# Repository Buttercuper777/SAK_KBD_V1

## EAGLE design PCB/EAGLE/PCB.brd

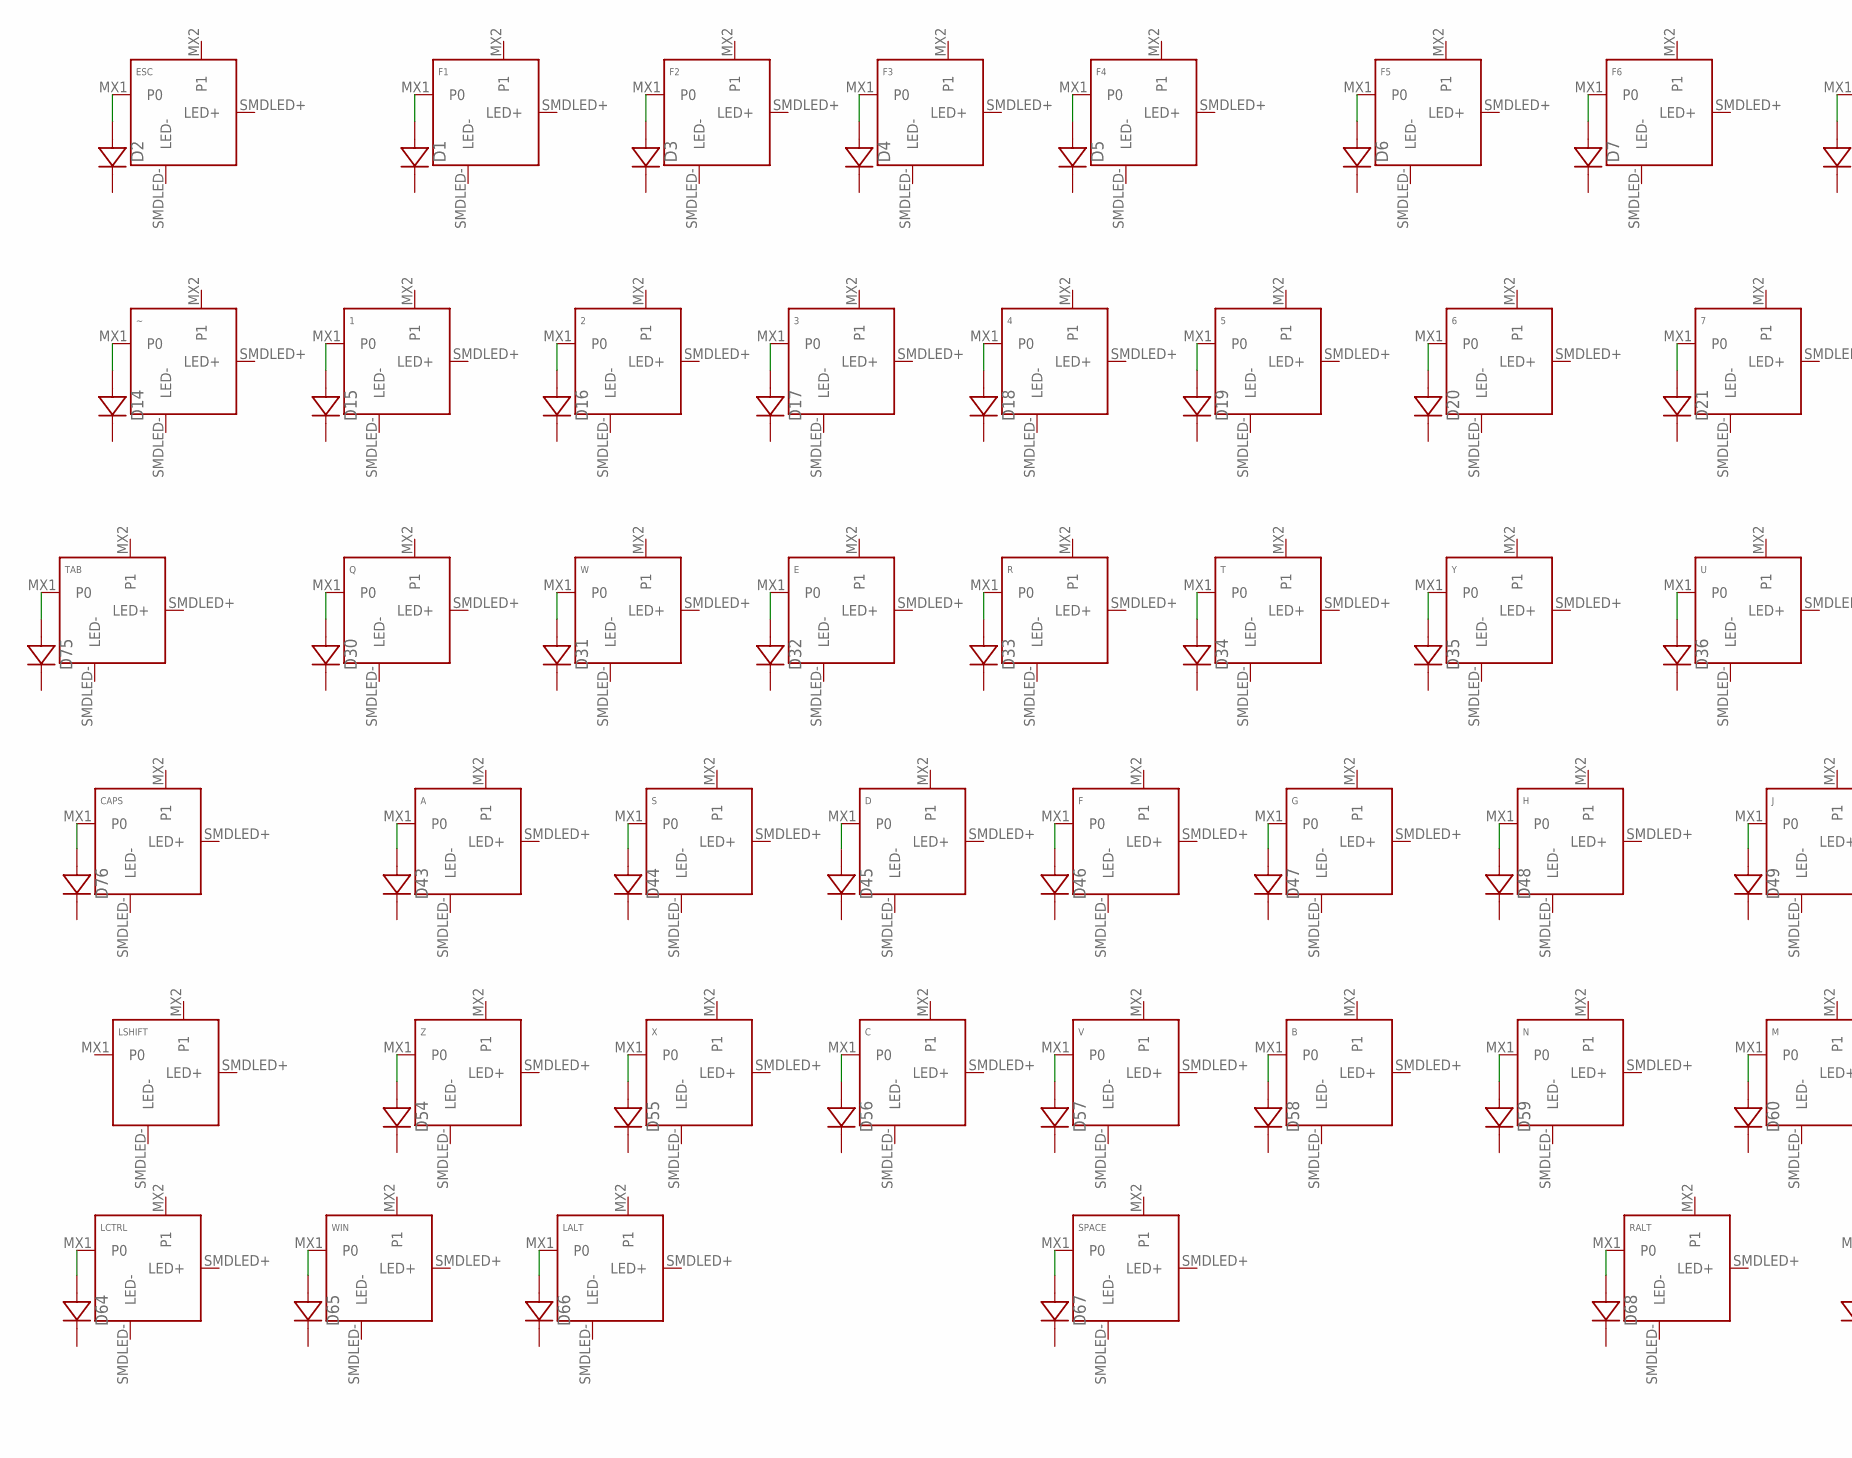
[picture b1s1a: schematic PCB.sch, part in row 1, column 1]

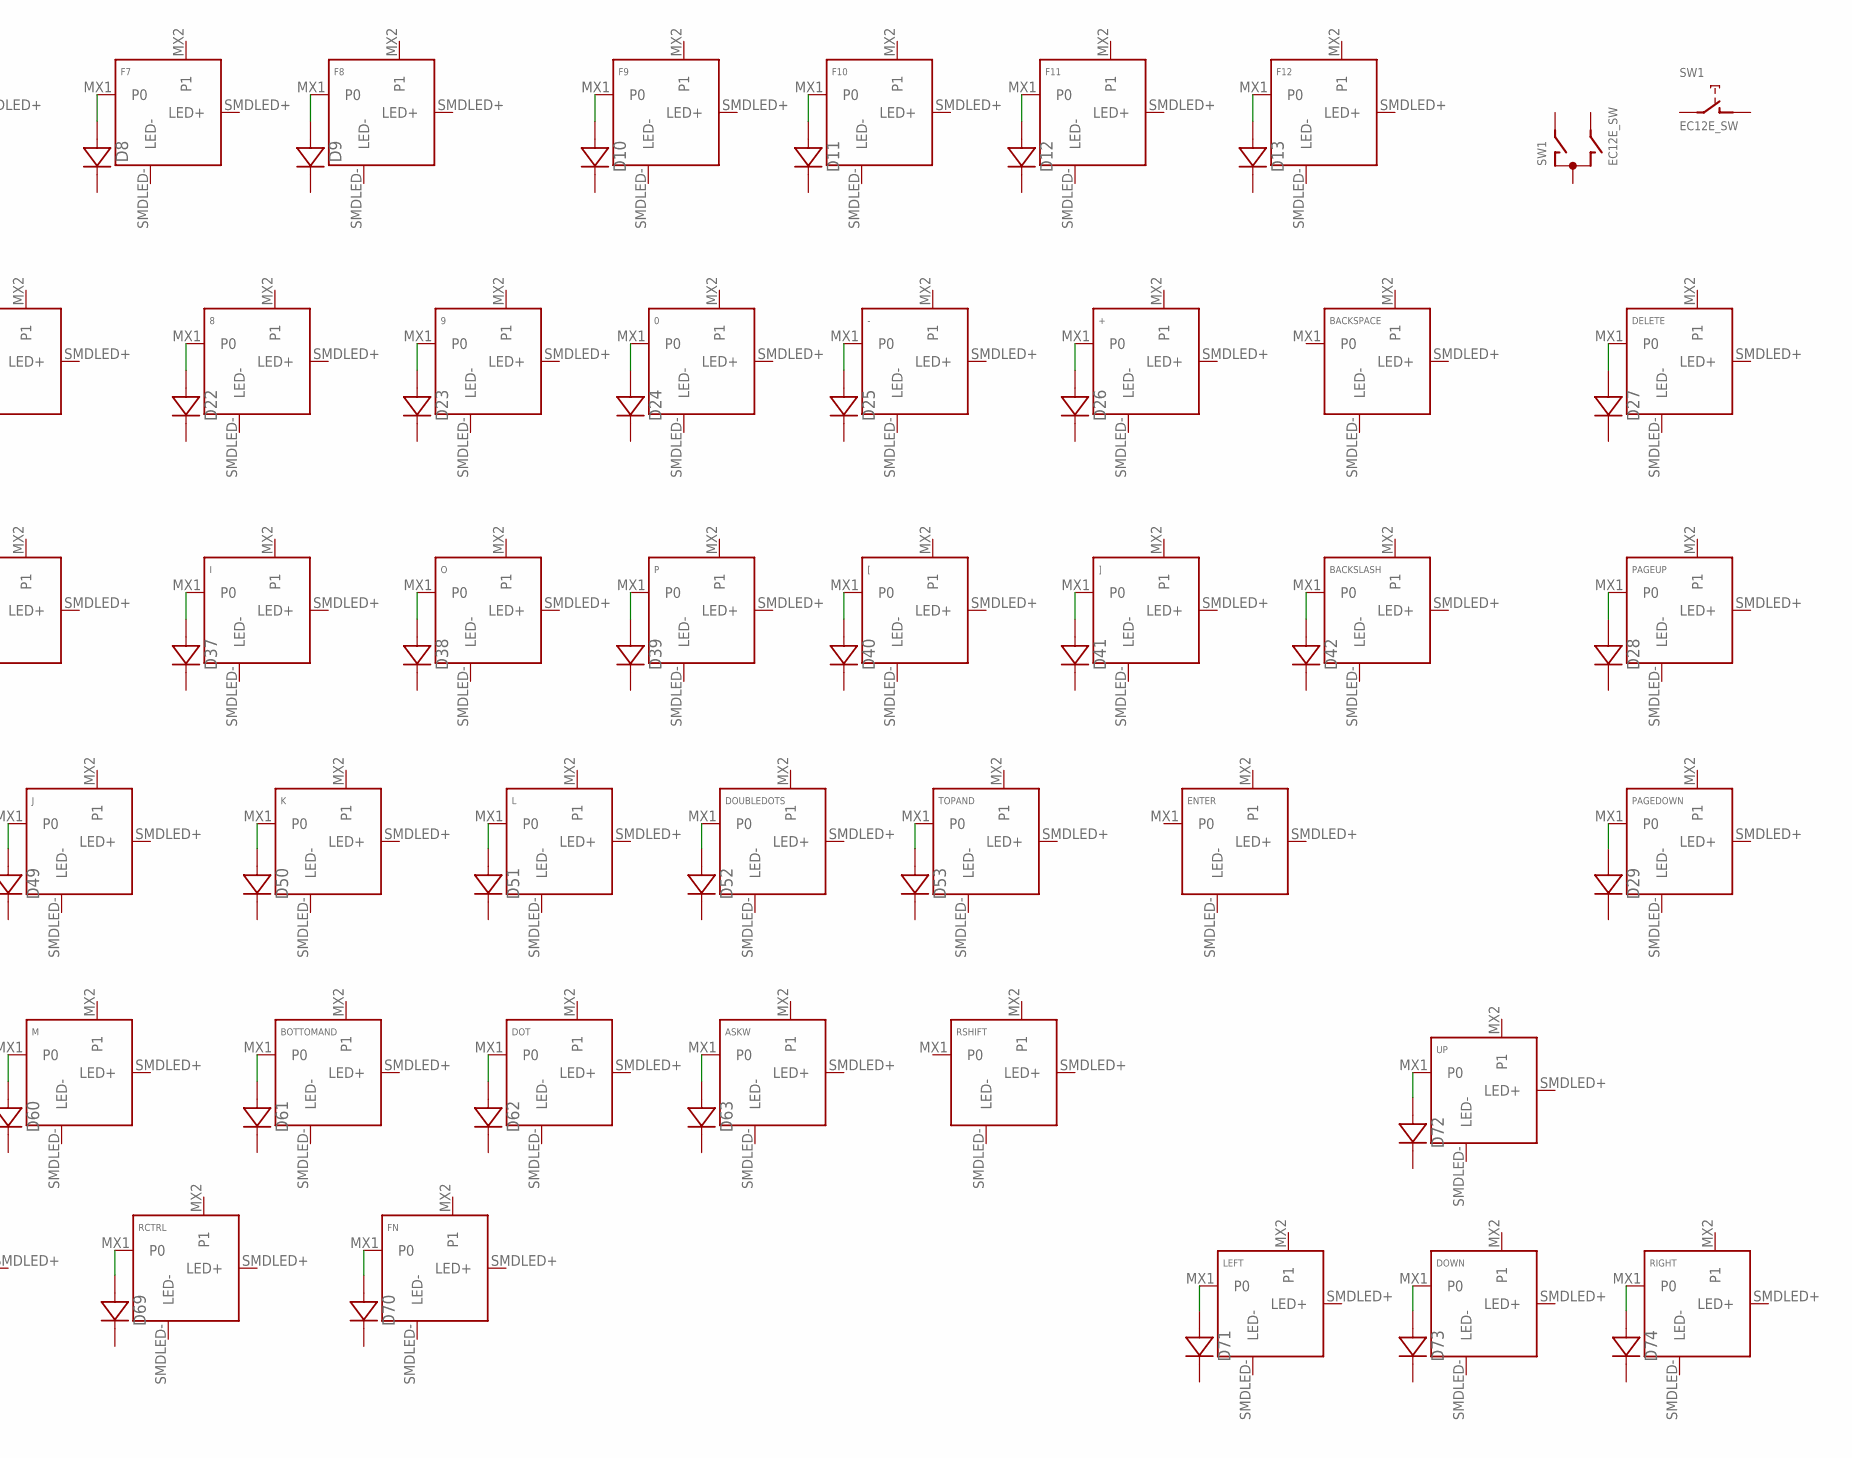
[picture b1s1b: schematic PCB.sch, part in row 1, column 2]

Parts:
0, 1, 2, 3, 4, 5, 6, 7, 8, 9: KEYSWITCH-SMDLED-MXHSPCB-1U-SMDLED; MXHSPCB-1U-SMDLED
+: KEYSWITCH-SMDLED-MXHSPCB-1U-SMDLED; MXHSPCB-1U-SMDLED
-: KEYSWITCH-SMDLED-MXHSPCB-1U-SMDLED; MXHSPCB-1U-SMDLED
A: KEYSWITCH-SMDLED-MXHSPCB-1U-SMDLED; MXHSPCB-1U-SMDLED
ASKW: KEYSWITCH-SMDLED-MXHSPCB-1U-SMDLED; MXHSPCB-1U-SMDLED
B: KEYSWITCH-SMDLED-MXHSPCB-1U-SMDLED; MXHSPCB-1U-SMDLED
BACKSLASH: KEYSWITCH-SMDLED-MXHSPCB-1U-SMDLED; MXHSPCB-1U-SMDLED
BACKSPACE: KEYSWITCH-SMDLED-MXHSPCB-2U-SMDLED; MXHSPCB-2U-SMDLED
BOTTOMAND: KEYSWITCH-SMDLED-MXHSPCB-1U-SMDLED; MXHSPCB-1U-SMDLED
C: KEYSWITCH-SMDLED-MXHSPCB-1U-SMDLED; MXHSPCB-1U-SMDLED
CAPS: KEYSWITCH-SMDLED-MXHSPCB-1U-SMDLED; MXHSPCB-1U-SMDLED
D: KEYSWITCH-SMDLED-MXHSPCB-1U-SMDLED; MXHSPCB-1U-SMDLED
D1, D2, D3, D4, D5, D6, D7, D8, D9, D10, D11, D12, D13, D14, D15, D16, D17, D18, D19, D20, D21, D22, D23, D24, D25, D26, D27, D28, D29, D30, D31, D32, D33, D34, D35, D36, D37, D38, D39, D40, D41, D42, D43, D44, D45, D46, D47, D48, D49, D50, D51, D52, D53, D54, D55, D56, D57, D58, D59, D60, D61, D62, D63, D64, D65, D66, D67, D68, D69, D70, D71, D72, D73, D74, D75, D76: DIODE-SOD-123; SOD-123
DELETE: KEYSWITCH-SMDLED-MXHSPCB-1U-SMDLED; MXHSPCB-1U-SMDLED
DOT: KEYSWITCH-SMDLED-MXHSPCB-1U-SMDLED; MXHSPCB-1U-SMDLED
DOUBLEDOTS: KEYSWITCH-SMDLED-MXHSPCB-1U-SMDLED; MXHSPCB-1U-SMDLED
DOWN: KEYSWITCH-SMDLED-MXHSPCB-1U-SMDLED; MXHSPCB-1U-SMDLED
E: KEYSWITCH-SMDLED-MXHSPCB-1U-SMDLED; MXHSPCB-1U-SMDLED
ENTER: KEYSWITCH-SMDLED-MXHSPCB-2U-SMDLED; MXHSPCB-2U-SMDLED
ESC: KEYSWITCH-SMDLED-MXHSPCB-1U-SMDLED; MXHSPCB-1U-SMDLED
F, F1, F2, F3, F4, F5, F6, F7, F8, F9, F10, F11, F12: KEYSWITCH-SMDLED-MXHSPCB-1U-SMDLED; MXHSPCB-1U-SMDLED
FN: KEYSWITCH-SMDLED-MXHSPCB-1U-SMDLED; MXHSPCB-1U-SMDLED
G: KEYSWITCH-SMDLED-MXHSPCB-1U-SMDLED; MXHSPCB-1U-SMDLED
H: KEYSWITCH-SMDLED-MXHSPCB-1U-SMDLED; MXHSPCB-1U-SMDLED
I: KEYSWITCH-SMDLED-MXHSPCB-1U-SMDLED; MXHSPCB-1U-SMDLED
J: KEYSWITCH-SMDLED-MXHSPCB-1U-SMDLED; MXHSPCB-1U-SMDLED
K: KEYSWITCH-SMDLED-MXHSPCB-1U-SMDLED; MXHSPCB-1U-SMDLED
L: KEYSWITCH-SMDLED-MXHSPCB-1U-SMDLED; MXHSPCB-1U-SMDLED
LALT: KEYSWITCH-SMDLED-MXHSPCB-1U-SMDLED; MXHSPCB-1U-SMDLED
LCTRL: KEYSWITCH-SMDLED-MXHSPCB-1U-SMDLED; MXHSPCB-1U-SMDLED
LEFT: KEYSWITCH-SMDLED-MXHSPCB-1U-SMDLED; MXHSPCB-1U-SMDLED
LSHIFT: KEYSWITCH-SMDLED-MXHSPCB-2U-SMDLED; MXHSPCB-2U-SMDLED
M: KEYSWITCH-SMDLED-MXHSPCB-1U-SMDLED; MXHSPCB-1U-SMDLED
N: KEYSWITCH-SMDLED-MXHSPCB-1U-SMDLED; MXHSPCB-1U-SMDLED
O: KEYSWITCH-SMDLED-MXHSPCB-1U-SMDLED; MXHSPCB-1U-SMDLED
P: KEYSWITCH-SMDLED-MXHSPCB-1U-SMDLED; MXHSPCB-1U-SMDLED
PAGEDOWN: KEYSWITCH-SMDLED-MXHSPCB-1U-SMDLED; MXHSPCB-1U-SMDLED
PAGEUP: KEYSWITCH-SMDLED-MXHSPCB-1U-SMDLED; MXHSPCB-1U-SMDLED
Q: KEYSWITCH-SMDLED-MXHSPCB-1U-SMDLED; MXHSPCB-1U-SMDLED
R: KEYSWITCH-SMDLED-MXHSPCB-1U-SMDLED; MXHSPCB-1U-SMDLED
RALT: KEYSWITCH-SMDLED-MXHSPCB-1U-SMDLED; MXHSPCB-1U-SMDLED
RCTRL: KEYSWITCH-SMDLED-MXHSPCB-1U-SMDLED; MXHSPCB-1U-SMDLED
RIGHT: KEYSWITCH-SMDLED-MXHSPCB-1U-SMDLED; MXHSPCB-1U-SMDLED
RSHIFT: KEYSWITCH-SMDLED-MXHSPCB-2U-SMDLED; MXHSPCB-2U-SMDLED
S: KEYSWITCH-SMDLED-MXHSPCB-1U-SMDLED; MXHSPCB-1U-SMDLED
SPACE: KEYSWITCH-SMDLED-MXHSPCB-6.25U-SMDLED-FLIPPED; MXHSPCB-6.25U-SMDLED-FLIPPED
SW1: EC12E_SW; ALPS_EC12E_SW
T: KEYSWITCH-SMDLED-MXHSPCB-1U-SMDLED; MXHSPCB-1U-SMDLED
TAB: KEYSWITCH-SMDLED-MXHSPCB-1U-SMDLED; MXHSPCB-1U-SMDLED
TOPAND: KEYSWITCH-SMDLED-MXHSPCB-1U-SMDLED; MXHSPCB-1U-SMDLED
U: KEYSWITCH-SMDLED-MXHSPCB-1U-SMDLED; MXHSPCB-1U-SMDLED
UP: KEYSWITCH-SMDLED-MXHSPCB-1U-SMDLED; MXHSPCB-1U-SMDLED
V: KEYSWITCH-SMDLED-MXHSPCB-1U-SMDLED; MXHSPCB-1U-SMDLED
W: KEYSWITCH-SMDLED-MXHSPCB-1U-SMDLED; MXHSPCB-1U-SMDLED
WIN: KEYSWITCH-SMDLED-MXHSPCB-1U-SMDLED; MXHSPCB-1U-SMDLED
X: KEYSWITCH-SMDLED-MXHSPCB-1U-SMDLED; MXHSPCB-1U-SMDLED
Y: KEYSWITCH-SMDLED-MXHSPCB-1U-SMDLED; MXHSPCB-1U-SMDLED
Z: KEYSWITCH-SMDLED-MXHSPCB-1U-SMDLED; MXHSPCB-1U-SMDLED
[: KEYSWITCH-SMDLED-MXHSPCB-1U-SMDLED; MXHSPCB-1U-SMDLED
]: KEYSWITCH-SMDLED-MXHSPCB-1U-SMDLED; MXHSPCB-1U-SMDLED
~: KEYSWITCH-SMDLED-MXHSPCB-1U-SMDLED; MXHSPCB-1U-SMDLED

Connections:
unnamed: D2.A, ESC.MX1 (P0)
unnamed: D1.A, F1.MX1 (P0)
unnamed: D3.A, F2.MX1 (P0)
unnamed: D4.A, F3.MX1 (P0)
unnamed: D5.A, F4.MX1 (P0)
unnamed: D6.A, F5.MX1 (P0)
unnamed: D7.A, F6.MX1 (P0)
unnamed: D8.A, F7.MX1 (P0)
unnamed: D9.A, F8.MX1 (P0)
unnamed: D10.A, F9.MX1 (P0)
unnamed: D11.A, F10.MX1 (P0)
unnamed: D12.A, F11.MX1 (P0)
unnamed: D13.A, F12.MX1 (P0)
unnamed: D14.A, ~.MX1 (P0)
unnamed: 1.MX1 (P0), D15.A
unnamed: 2.MX1 (P0), D16.A
unnamed: 3.MX1 (P0), D17.A
unnamed: 4.MX1 (P0), D18.A
unnamed: 5.MX1 (P0), D19.A
unnamed: 6.MX1 (P0), D20.A
unnamed: 7.MX1 (P0), D21.A
unnamed: 8.MX1 (P0), D22.A
unnamed: 9.MX1 (P0), D23.A
unnamed: 0.MX1 (P0), D24.A
unnamed: -.MX1 (P0), D25.A
unnamed: +.MX1 (P0), D26.A
unnamed: D27.A, DELETE.MX1 (P0)
unnamed: D28.A, PAGEUP.MX1 (P0)
unnamed: D29.A, PAGEDOWN.MX1 (P0)
unnamed: D30.A, Q.MX1 (P0)
unnamed: D31.A, W.MX1 (P0)
unnamed: D32.A, E.MX1 (P0)
unnamed: D33.A, R.MX1 (P0)
unnamed: D34.A, T.MX1 (P0)
unnamed: D35.A, Y.MX1 (P0)
unnamed: D36.A, U.MX1 (P0)
unnamed: D37.A, I.MX1 (P0)
unnamed: D38.A, O.MX1 (P0)
unnamed: D39.A, P.MX1 (P0)
unnamed: D40.A, [.MX1 (P0)
unnamed: D41.A, ].MX1 (P0)
unnamed: BACKSLASH.MX1 (P0), D42.A
unnamed: A.MX1 (P0), D43.A
unnamed: D44.A, S.MX1 (P0)
unnamed: D.MX1 (P0), D45.A
unnamed: D46.A, F.MX1 (P0)
unnamed: D47.A, G.MX1 (P0)
unnamed: D48.A, H.MX1 (P0)
unnamed: D49.A, J.MX1 (P0)
unnamed: D50.A, K.MX1 (P0)
unnamed: D51.A, L.MX1 (P0)
unnamed: D52.A, DOUBLEDOTS.MX1 (P0)
unnamed: D53.A, TOPAND.MX1 (P0)
unnamed: D54.A, Z.MX1 (P0)
unnamed: D55.A, X.MX1 (P0)
unnamed: C.MX1 (P0), D56.A
unnamed: D57.A, V.MX1 (P0)
unnamed: B.MX1 (P0), D58.A
unnamed: D59.A, N.MX1 (P0)
unnamed: D60.A, M.MX1 (P0)
unnamed: BOTTOMAND.MX1 (P0), D61.A
unnamed: D62.A, DOT.MX1 (P0)
unnamed: ASKW.MX1 (P0), D63.A
unnamed: D64.A, LCTRL.MX1 (P0)
unnamed: D65.A, WIN.MX1 (P0)
unnamed: D66.A, LALT.MX1 (P0)
unnamed: D67.A, SPACE.MX1 (P0)
unnamed: D68.A, RALT.MX1 (P0)
unnamed: D69.A, RCTRL.MX1 (P0)
unnamed: D70.A, FN.MX1 (P0)
unnamed: D71.A, LEFT.MX1 (P0)
unnamed: D72.A, UP.MX1 (P0)
unnamed: D73.A, DOWN.MX1 (P0)
unnamed: D74.A, RIGHT.MX1 (P0)
unnamed: D75.A, TAB.MX1 (P0)
unnamed: CAPS.MX1 (P0), D76.A

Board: 2 copper layers, 157 parts (0 on the bottom side), 76 nets, no tracks yet.

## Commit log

2021-01-20 1st_load
2021-01-21 D_groups
